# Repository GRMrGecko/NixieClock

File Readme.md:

#Nixie Tube Clock - Arduino Controlled Clock

I don't have any fun names to put on this project, I haven't thought of one... If you have one, email me.

All details has not been written out, but you can piece together things by going to my blog at http://mrgecko.org and viewing images and docs here.

You would want to use Modified Board to print as I include the needed gerber files and also it has pin outs for power which is useful for adding the bluetooth board.

Many of the parts used is available at https://www.sparkfun.com/wish_lists/83348 I recommend buying the needed resistors from some place where you can order them individually.

To get nixie tubes, I recommend you go on ebay and search for "Nixie Tube IN 14" without quotes.

Power Supply can be ordered from http://www.allspectrum.com/store/nixie-power-supply-high-voltage-switch-mode-dc-dc-converter-kit-95-190vdc-25ma-180vdc-p-521.html
The tube ICs can be purchased from http://www.allspectrum.com/store/74141-nixie-tube-driver-ic-russian-p-211.html, you will need 6.

Look at notes.txt for resister values.

Extended documents available at https://sf.gec.im/d/1c3d227302/

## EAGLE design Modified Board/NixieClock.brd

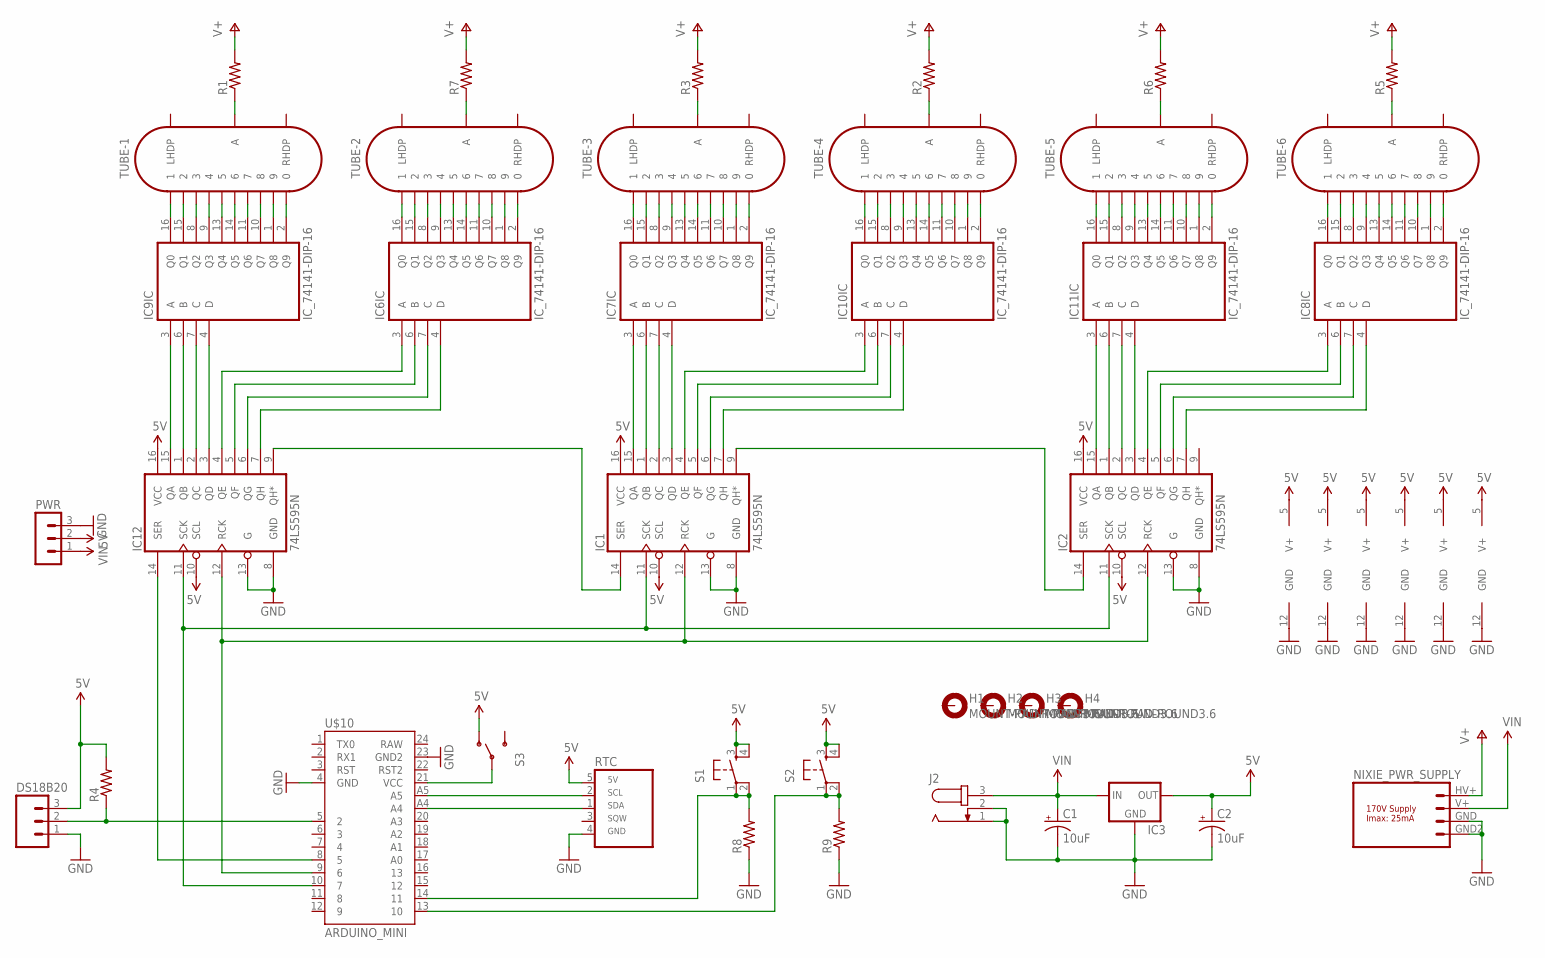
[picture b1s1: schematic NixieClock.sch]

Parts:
C1, C2: 10uF; CPOL-RADIAL-10UF-25V
DS18B20: DS18B20DS18B20; DS18B20
H1, H2, H3, H4: MOUNT-PAD-ROUND3.6; 3,6-PAD
IC1, IC2, IC12: 74LS595N; DIL16
IC3: V_REG_78XXSIDE; 78XXL
IC6, IC7, IC8, IC9, IC10, IC11: IC_74141-DIP-16; DIL16
J2: JACK-PLUG0; SPC4077
NIXIE_PWR_SUPPLY: NIXIE_PWR_SUPPLYPTH; NIXIE_PWR_SUPPLY
PWR: MA03-1
R1, R2, R3, R4, R5, R6, R7, R8, R9: RESISTORPTH-1/4W; AXIAL-0.4
RTC: SCOTT_RTCPTH; SCOTT_RTC
S1, S2: TAC_SWITCHPTH; TACTILE-PTH
S3: SWITCH-SPDTPTH; SWITCH-SPDT
TUBE-1, TUBE-2, TUBE-3, TUBE-4, TUBE-5, TUBE-6: IN-14
U$10: ARDUINO_MINI

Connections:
5V: C2.1 (+), DS18B20.3 (5V), IC1.10 (SCL), IC1.16 (VCC), IC2.10 (SCL), IC2.16 (VCC), IC3.OUT, IC6.5 (V+), IC7.5 (V+), IC8.5 (V+), IC9.5 (V+), IC10.5 (V+), IC11.5 (V+), IC12.10 (SCL), IC12.16 (VCC), PWR.2, R4.P$2 (2), RTC.5 (5V), S1.3, S1.4, S2.3, S2.4, S3.1 (O)
GND: C1.2 (-), C2.2 (-), DS18B20.1 (GND), IC1.8 (GND), IC1.13 (G), IC2.8 (GND), IC2.13 (G), IC3.GND, IC6.12 (GND), IC7.12 (GND), IC8.12 (GND), IC9.12 (GND), IC10.12 (GND), IC11.12 (GND), IC12.8 (GND), IC12.13 (G), J2.1, J2.2, NIXIE_PWR_SUPPLY.GND (4), NIXIE_PWR_SUPPLY.GND2 (1), PWR.3, R8.P$1 (1), R9.P$1 (1), RTC.4 (GND), U$10.4 (GND), U$10.23 (GND2)
unnamed: R1.P$1 (1), TUBE-1.A
unnamed: R7.P$1 (1), TUBE-2.A
unnamed: R3.P$1 (1), TUBE-3.A
unnamed: R2.P$1 (1), TUBE-4.A
unnamed: R6.P$1 (1), TUBE-5.A
unnamed: R5.P$1 (1), TUBE-6.A
unnamed: IC9.16 (Q0), TUBE-1.1
unnamed: IC9.15 (Q1), TUBE-1.2
unnamed: IC9.8 (Q2), TUBE-1.3
unnamed: IC9.9 (Q3), TUBE-1.4
unnamed: IC9.13 (Q4), TUBE-1.5
unnamed: IC9.14 (Q5), TUBE-1.6
unnamed: IC9.11 (Q6), TUBE-1.7
unnamed: IC9.10 (Q7), TUBE-1.8
unnamed: IC9.1 (Q8), TUBE-1.9
unnamed: IC9.2 (Q9), TUBE-1.0
unnamed: IC6.16 (Q0), TUBE-2.1
unnamed: IC6.15 (Q1), TUBE-2.2
unnamed: IC6.8 (Q2), TUBE-2.3
unnamed: IC6.9 (Q3), TUBE-2.4
unnamed: IC6.13 (Q4), TUBE-2.5
unnamed: IC6.14 (Q5), TUBE-2.6
unnamed: IC6.11 (Q6), TUBE-2.7
unnamed: IC6.10 (Q7), TUBE-2.8
unnamed: IC6.1 (Q8), TUBE-2.9
unnamed: IC6.2 (Q9), TUBE-2.0
unnamed: IC7.16 (Q0), TUBE-3.1
unnamed: IC7.15 (Q1), TUBE-3.2
unnamed: IC7.8 (Q2), TUBE-3.3
unnamed: IC7.9 (Q3), TUBE-3.4
unnamed: IC7.13 (Q4), TUBE-3.5
unnamed: IC7.14 (Q5), TUBE-3.6
unnamed: IC7.11 (Q6), TUBE-3.7
unnamed: IC7.10 (Q7), TUBE-3.8
unnamed: IC7.1 (Q8), TUBE-3.9
unnamed: IC7.2 (Q9), TUBE-3.0
unnamed: IC10.16 (Q0), TUBE-4.1
unnamed: IC10.15 (Q1), TUBE-4.2
unnamed: IC10.8 (Q2), TUBE-4.3
unnamed: IC10.9 (Q3), TUBE-4.4
unnamed: IC10.13 (Q4), TUBE-4.5
unnamed: IC10.14 (Q5), TUBE-4.6
unnamed: IC10.11 (Q6), TUBE-4.7
unnamed: IC10.10 (Q7), TUBE-4.8
unnamed: IC10.1 (Q8), TUBE-4.9
unnamed: IC10.2 (Q9), TUBE-4.0
unnamed: IC11.16 (Q0), TUBE-5.1
unnamed: IC11.15 (Q1), TUBE-5.2
unnamed: IC11.8 (Q2), TUBE-5.3
unnamed: IC11.9 (Q3), TUBE-5.4
unnamed: IC11.13 (Q4), TUBE-5.5
unnamed: IC11.14 (Q5), TUBE-5.6
unnamed: IC11.11 (Q6), TUBE-5.7
unnamed: IC11.10 (Q7), TUBE-5.8
unnamed: IC11.1 (Q8), TUBE-5.9
unnamed: IC11.2 (Q9), TUBE-5.0
unnamed: IC8.16 (Q0), TUBE-6.1
unnamed: IC8.15 (Q1), TUBE-6.2
unnamed: IC8.8 (Q2), TUBE-6.3
unnamed: IC8.9 (Q3), TUBE-6.4
unnamed: IC8.13 (Q4), TUBE-6.5
unnamed: IC8.14 (Q5), TUBE-6.6
unnamed: IC8.11 (Q6), TUBE-6.7
unnamed: IC8.10 (Q7), TUBE-6.8
unnamed: IC8.1 (Q8), TUBE-6.9
unnamed: IC8.2 (Q9), TUBE-6.0
unnamed: IC1.1 (QB), IC7.6 (B)
unnamed: IC1.2 (QC), IC7.7 (C)
unnamed: IC1.3 (QD), IC7.4 (D)
unnamed: IC1.15 (QA), IC7.3 (A)
unnamed: IC9.6 (B), IC12.1 (QB)
unnamed: IC9.7 (C), IC12.2 (QC)
unnamed: IC9.4 (D), IC12.3 (QD)
unnamed: IC9.3 (A), IC12.15 (QA)
unnamed: IC2.1 (QB), IC11.6 (B)
unnamed: IC2.2 (QC), IC11.7 (C)
unnamed: IC2.3 (QD), IC11.4 (D)
unnamed: IC2.15 (QA), IC11.3 (A)
unnamed: IC6.3 (A), IC12.4 (QE)
unnamed: IC6.6 (B), IC12.5 (QF)
unnamed: IC6.7 (C), IC12.6 (QG)
unnamed: IC6.4 (D), IC12.7 (QH)
unnamed: IC1.14 (SER), IC12.9 (QH*)
unnamed: IC1.9 (QH*), IC2.14 (SER)
unnamed: IC1.4 (QE), IC10.3 (A)
unnamed: IC1.5 (QF), IC10.6 (B)
unnamed: IC1.6 (QG), IC10.7 (C)
unnamed: IC1.7 (QH), IC10.4 (D)
unnamed: IC12.14 (SER), U$10.8 (5)
unnamed: IC2.4 (QE), IC8.3 (A)
unnamed: IC2.5 (QF), IC8.6 (B)
unnamed: IC2.6 (QG), IC8.7 (C)
unnamed: IC2.7 (QH), IC8.4 (D)
unnamed: IC1.11 (SCK), IC2.11 (SCK), IC12.11 (SCK), U$10.10 (7)
unnamed: IC1.12 (RCK), IC2.12 (RCK), IC12.12 (RCK), U$10.9 (6)
unnamed: R9.P$2 (2), S2.1, S2.2, U$10.13 (10)
unnamed: DS18B20.2 (DS), R4.P$1 (1), U$10.5 (2)
unnamed: RTC.2 (SCL), U$10.A5
unnamed: RTC.1 (SDA), U$10.A4
unnamed: S3.2, U$10.21 (VCC)
unnamed: R8.P$2 (2), S1.1, S1.2, U$10.14 (11)
V+: NIXIE_PWR_SUPPLY.HV+ (3), R1.P$2 (2), R2.P$2 (2), R3.P$2 (2), R5.P$2 (2), R6.P$2 (2), R7.P$2 (2)
VIN: C1.1 (+), IC3.IN, J2.3, NIXIE_PWR_SUPPLY.V+ (2), PWR.1

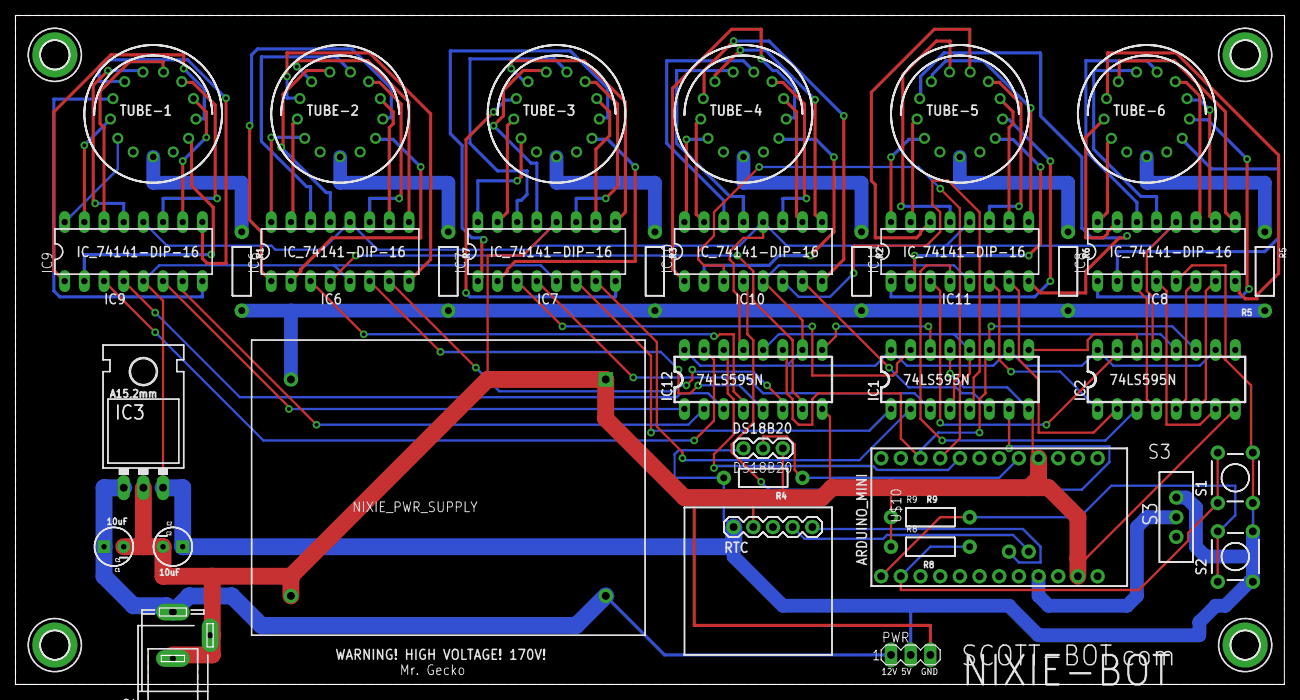
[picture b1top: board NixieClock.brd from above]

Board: 2 copper layers, 163.8 x 86.4 mm, 40 parts (0 on the bottom side), 105 nets.

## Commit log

2014-08-19 Nixie Clock Start
2015-04-14 Fixed URL for extended documentation

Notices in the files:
parts and their libraries:
SparkFun: Licensing: CC v3.0 Share-Alike You are welcome to use this library for commercial purposes.
